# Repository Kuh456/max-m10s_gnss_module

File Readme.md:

> [!WARNING]
> Kicad v9を用いて作成したため、これ以下のバージョンのkicadだと動きません

## 使用部品

| 部品名 | 個数 | URL |
| --- | --- | --- |
| MAX-M10S | 1 | https://www.digikey.jp/ja/products/detail/u-blox/MAX-M10S-00B/15712906 |
| RT9080 3.3V レギュレーター | 1 | https://akizukidenshi.com/catalog/g/g129588/ |
| 1608 コンデンサ 4.7pF | 1 | - |
| 1608 コンデンサ 10nF | 1 | - |
| 1608 コンデンサ 0.1uF | 2 | https://akizukidenshi.com/catalog/g/g113374/ |
| 1608 コンデンサ 1uF | 2 | - |
| 1608 コンデンサ 10uF | 2 | https://akizukidenshi.com/catalog/g/g113161/ |
| 1608 抵抗 10Ω | 1 | - |
| 1608 抵抗 33Ω | 2 | - |
| 1608 抵抗 1kΩ | 2 | - |
| 1608 抵抗 2.2kΩ | 2 | - |
| フェライトビーズ 4.3nH | 1 | - |
| u.FL コネクタ | 1 | https://akizukidenshi.com/catalog/g/g115417/ |
| 1608 逆流防止ダイオード | 1 | - |

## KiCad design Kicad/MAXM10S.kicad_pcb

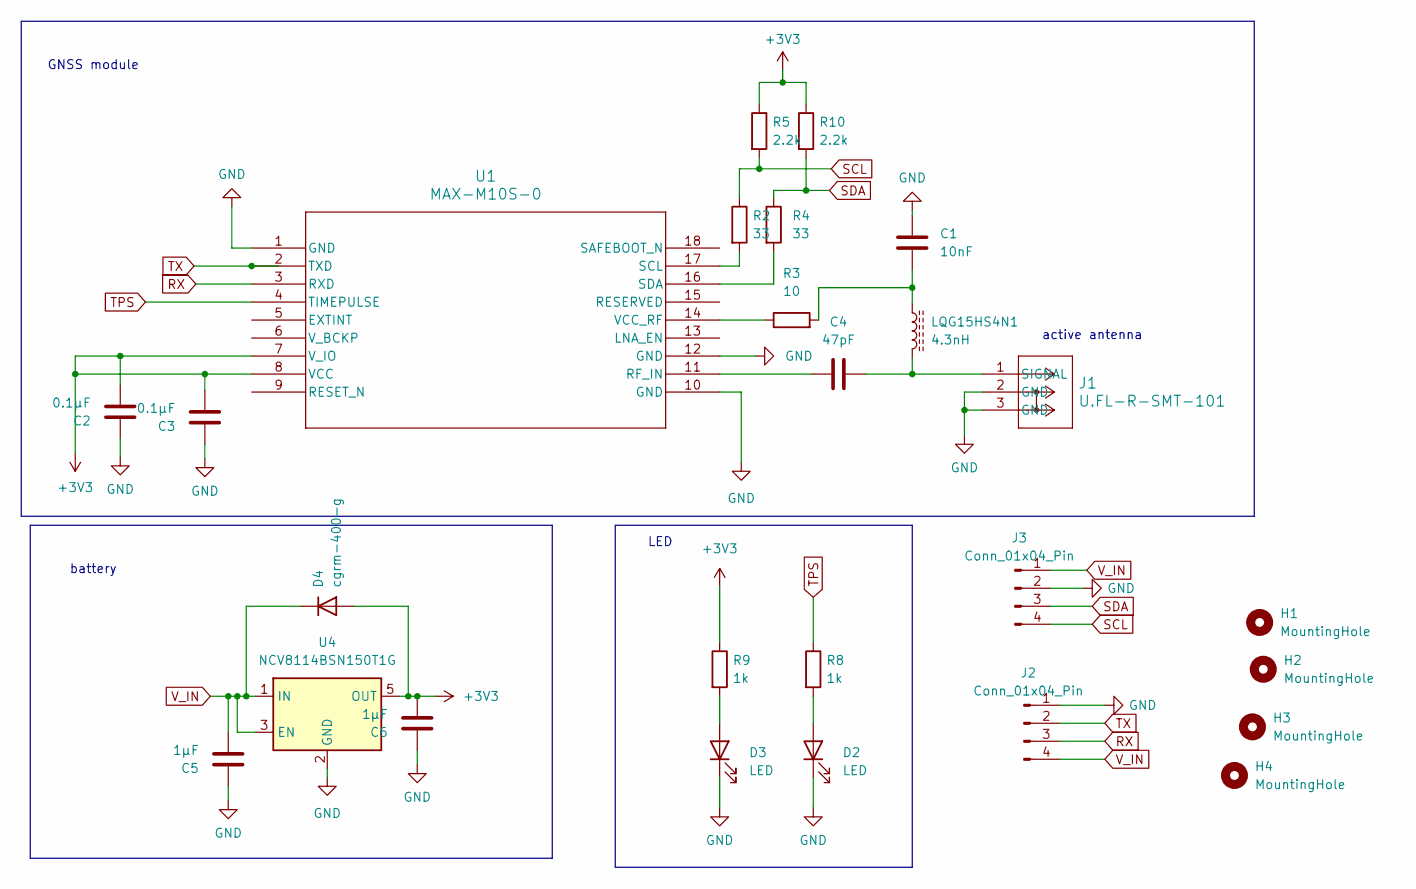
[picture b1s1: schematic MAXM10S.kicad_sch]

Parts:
C1: 10nF; C_0603_1608Metric
C2, C3: 0.1μF; C_0603_1608Metric
C4: 47pF; C_0603_1608Metric
C5, C6: 1μF; C_0603_1608Metric
D2, D3: LED; LED_0603_1608Metric
D4: cgrm-400-g; D_0603_1608Metric
H1, H2, H3, H4: MountingHole; MountingHole_3mm
J1: U.FL-R-SMT-101; COAX2_U.FL-R-SMT-101_HIR
J2, J3: Conn_01x04_Pin; PinHeader_1x04_P2.54mm_Vertical
LQG15HS4N1: 4.3nH; L_0402_1005Metric
R2, R4: 33; R_0603_1608Metric
R3: 10; R_0603_1608Metric
R5, R10: 2.2k; R_0603_1608Metric
R8, R9: 1k; R_0603_1608Metric
U1: MAX-M10S-0; SMT_M10S-0_UBL
U4: NCV8114BSN150T1G; TSOT-23-5_HandSoldering

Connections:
+3V3: C2.2, C3.2, C6.2, D4.2 (A), R5.1, R9.1, R10.1, U1.7 (V_IO), U1.8 (VCC), U4.5 (OUT)
GND: C1.1, C2.1, C3.1, C5.1, C6.1, D2.1 (K), D3.1 (K), J1.2 (GND), J1.3 (GND), J2.1, J3.2, U1.1 (GND), U1.10 (GND), U1.12 (GND), U4.2 (GND)
unnamed: C1.2, LQG15HS4N1.1, R3.2
unnamed: D2.2 (A), R8.2
unnamed: D3.2 (A), R9.2
unnamed: C4.1, J1.1 (SIGNAL), LQG15HS4N1.2
unnamed: C4.2, U1.11 (RF_IN)
unnamed: R2.2, U1.17 (SCL)
unnamed: R4.2, U1.16 (SDA)
unnamed: R3.1, U1.14 (VCC_RF)
RX: J2.3, U1.3 (RXD)
SCL: J3.4, R2.1, R5.2
SDA: J3.3, R4.1, R10.2
TPS: R8.1, U1.4 (TIMEPULSE)
TX: J2.2, U1.2 (TXD)
V_IN: C5.2, D4.1 (K), J2.4, J3.1, U4.1 (IN), U4.3 (EN)

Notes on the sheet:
LED
GNSS module
active antenna
battery

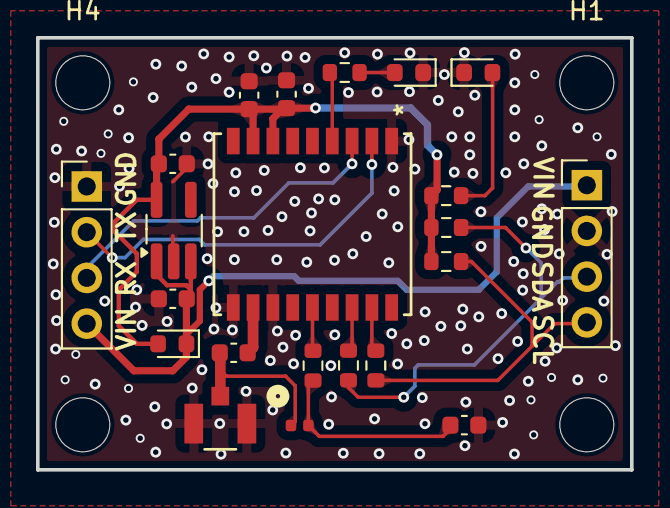
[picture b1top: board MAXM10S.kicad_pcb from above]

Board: 8 copper layers, 33.0 x 24.0 mm, 26 parts (0 on the bottom side), 16 nets.

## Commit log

2026-01-12 feat: add Readme
2026-01-12 fix: Markdownの崩れを修正
2026-01-12 add: 3dcad
2026-01-12 fix:typo
2026-01-13 Update compatibility warning in Readme.md
    Remove warning about compatibility with Kicad versions.
